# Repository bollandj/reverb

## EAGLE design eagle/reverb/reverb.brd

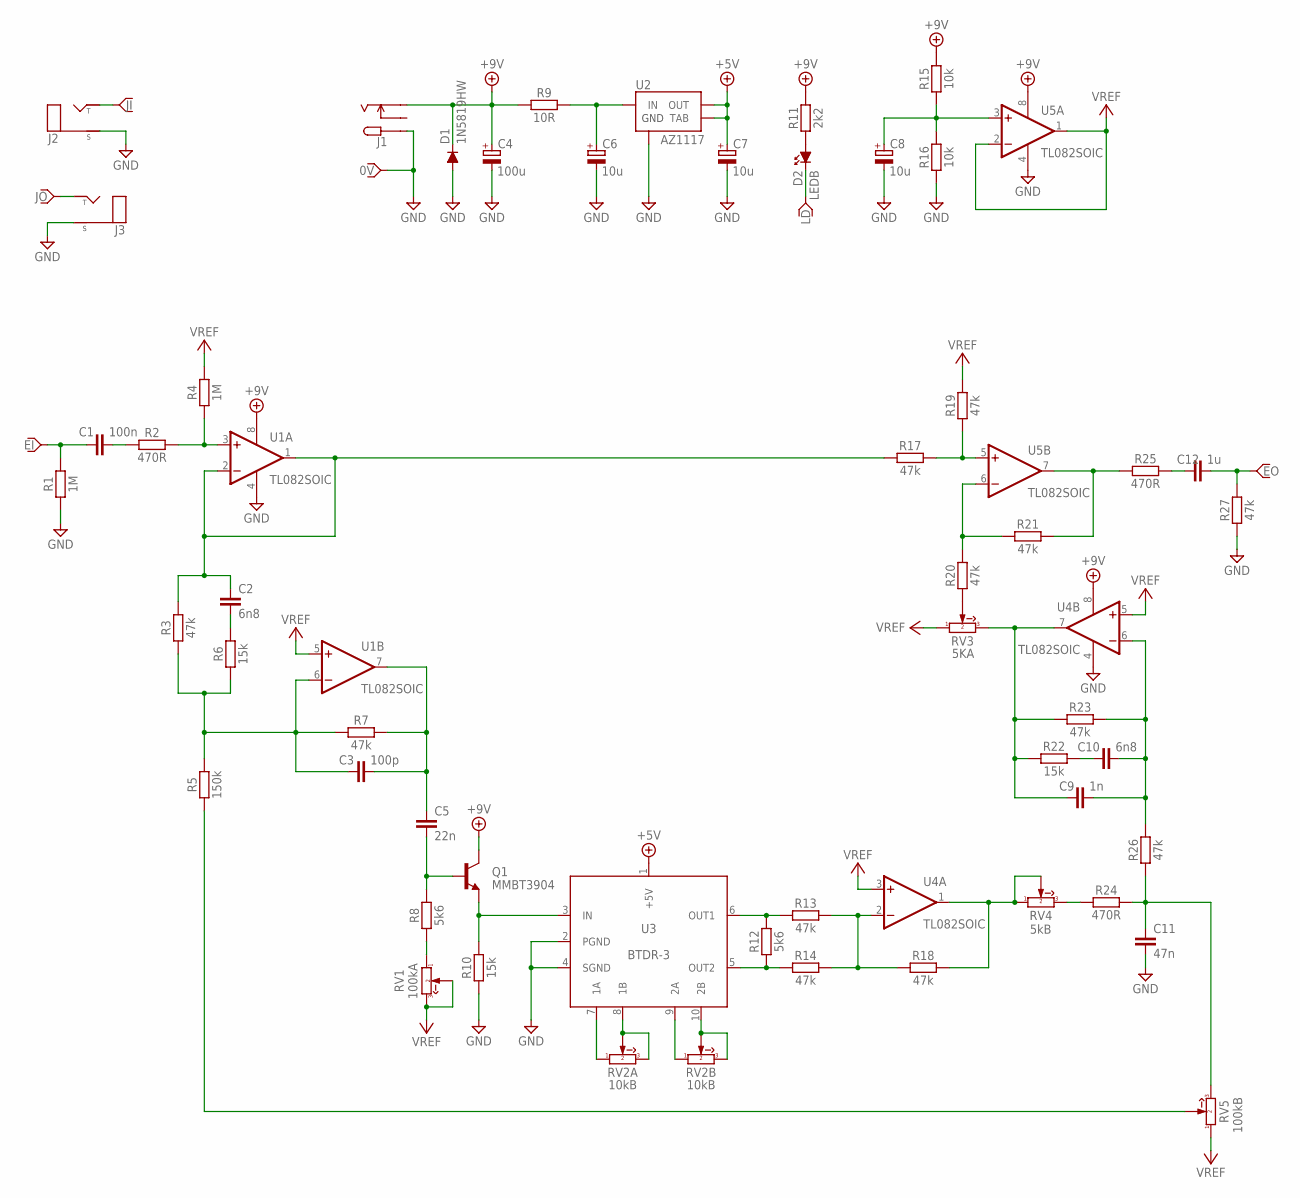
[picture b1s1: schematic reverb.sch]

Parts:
C1: 100n; C_0603
C2, C10: 6n8; C_0603
C3: 100p; C_0603
C4: 100u; C_E_TH_5MM
C5: 22n; C_0603
C6, C7, C8: 10u; C_E_TH_5MM
C9: 1n; C_0603
C11: 47n; C_0603
C12: 1u; C_0603
D1: 1N5819HW; SOD123
D2: LEDB; LED_5MM
J1: DC_JACK_C2; DC_JACK_CON_2MM
J2, J3: MONOJACK2MM; MONOJACK_CON_2MM
P1: 0V; CON_PIN
P2: LD; CON_PIN
P3: JO; CON_PIN
P4: JI; CON_PIN
P5: EO; CON_PIN
P6: EI; CON_PIN
Q1: MMBT3904; SOT23
R1, R4: 1M; R_0603
R2, R24, R25: 470R; R_0603
R3, R7, R13, R14, R17, R18, R19, R20, R21, R23, R26, R27: 47k; R_0603
R5: 150k; R_0603
R6, R10, R22: 15k; R_0603
R8, R12: 5k6; R_0603
R9: 10R; R_0603
R11: 2k2; R_0603
R15, R16: 10k; R_0603
RV1: 100kA; R_V_ALPHA_PCB_16MM
RV2: 10kB; R_V_ALPHA_PCB_16MM_DUAL
RV3: 5KA; R_V_ALPHA_PCB_16MM
RV4: 5kB; R_V_ALPHA_PCB_16MM
RV5: 100kB; R_V_ALPHA_PCB_16MM
U1, U4, U5: TL082SOIC; SOIC8
U2: AZ1117; SOT223
U3: BTDR-3

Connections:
+5V: C7.+VE (+), U2.2 (OUT), U2.4 (TAB), U3.1 (+5V)
+9V: C4.+VE (+), D1.C, J1.S, Q1.3 (C), R9.2, R11.2, R15.2, U1.8 (V+), U4.8 (V+), U5.8 (V+)
GND: C4.-VE (-), C6.-VE (-), C7.-VE (-), C8.-VE (-), C11.1, D1.A, J1.T, J2.S, J3.S, P1.1, R1.1, R10.1, R16.1, R27.1, U1.4 (V-), U2.1 (GND), U3.2 (PGND), U3.4 (SGND), U4.4 (V-), U5.4 (V-)
unnamed: C11.2, R24.2, R26.1, RV5.3
unnamed: C8.+VE (+), R15.1, R16.2, U5.3 (+IN)
unnamed: C1.1, R2.1
unnamed: R2.2, R4.1, U1.3 (+IN)
unnamed: C1.2, P6.1, R1.2
unnamed: R17.2, R19.1, U5.5 (+IN)
unnamed: R20.2, R21.1, U5.6 (-IN)
unnamed: R21.2, R25.1, U5.7 (OUT)
unnamed: C12.2, R25.2
unnamed: C12.1, P5.1, R27.2
unnamed: C3.1, C5.2, R7.2, U1.7 (OUT)
unnamed: R24.1, RV4.3
unnamed: C2.1, R6.2
unnamed: C5.1, Q1.1 (B), R8.2
unnamed: Q1.2 (E), R10.2, U3.3 (IN)
unnamed: RV2.A1 (1), U3.7 (1A)
unnamed: RV2.A2 (2), RV2.A3 (3), U3.8 (1B)
unnamed: RV2.B1 (1), U3.9 (2A)
unnamed: RV2.B2 (2), RV2.B3 (3), U3.10 (2B)
unnamed: R12.2, R13.1, U3.6 (OUT1)
unnamed: R12.1, R14.1, U3.5 (OUT2)
unnamed: R13.2, R14.2, R18.1, U4.2 (-IN)
unnamed: R18.2, RV4.1, RV4.2, U4.1 (OUT)
unnamed: C6.+VE (+), R9.1, U2.3 (IN)
unnamed: C2.2, R3.2, R17.1, U1.1 (OUT), U1.2 (-IN)
unnamed: C9.2, R22.1, R23.1, RV3.3, U4.7 (OUT)
unnamed: R8.1, RV1.1
unnamed: C9.1, C10.1, R23.2, R26.2, U4.6 (-IN)
unnamed: C10.2, R22.2
unnamed: R20.1, RV3.2
unnamed: R5.1, RV5.2
unnamed: J3.T, P3.1
unnamed: D2.A, R11.1
unnamed: J2.T, P4.1
unnamed: C3.2, R3.1, R5.2, R6.1, R7.1, U1.6 (-IN)
unnamed: D2.C, P2.1
VREF: R4.2, R19.2, RV1.2, RV1.3, RV3.1, RV5.1, U1.5 (+IN), U4.3 (+IN), U4.5 (+IN), U5.1 (OUT), U5.2 (-IN)

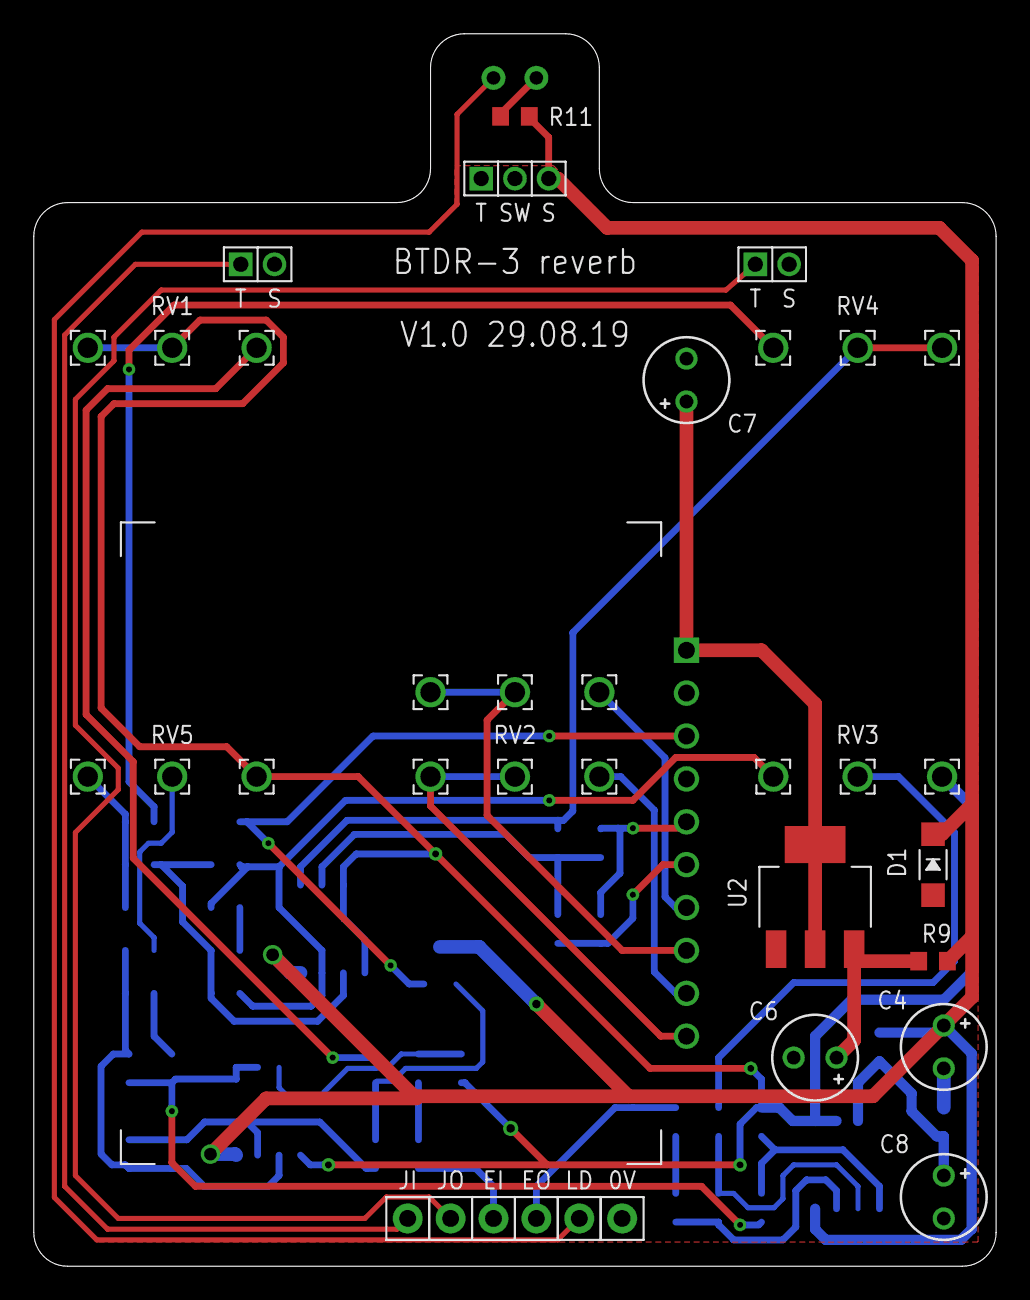
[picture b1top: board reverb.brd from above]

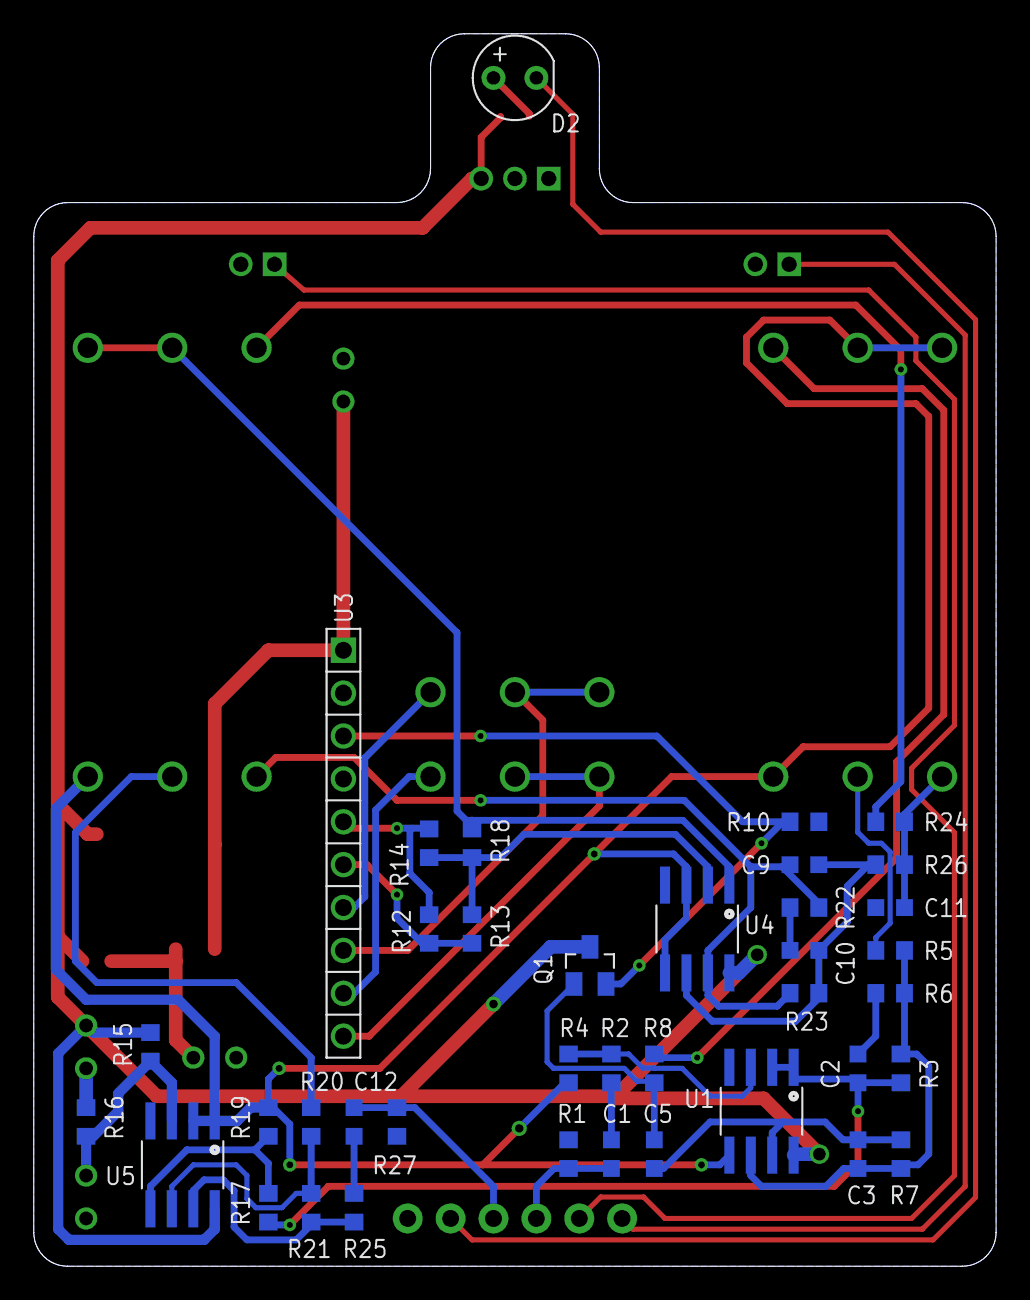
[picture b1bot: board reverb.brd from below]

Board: 2 copper layers, 57.0 x 73.0 mm, 61 parts (43 on the bottom side), 40 nets.
